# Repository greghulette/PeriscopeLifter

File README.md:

# PeriscopeLifter
Files and Basic Instructions for my Periscope Lifter

Latest version is V0.4

The latest instructions can be found here: https://docs.google.com/document/d/1gkrul7UIyUIZ05SwGsmy0yHRKMRutKzC-wxl7RRob7I/edit?usp=sharing

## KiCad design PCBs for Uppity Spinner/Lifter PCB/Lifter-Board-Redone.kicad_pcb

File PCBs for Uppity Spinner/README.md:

# PeriscopeLifter
Here are the files for the PCBs that I modified for the Open Source Periscope Lifter.  All these files were created with KiCad so you may need to download them if you want to open them, or there is a Gerber folder that you can use to have them manufactured.   

The Lifter board is a slightly modified PCB from the original one.  I had added some 5V outputs and a serial port header.  Mimir has since incorporated these into his designs.  You may use this PCB or his, providing his is utilizing the Silicone Ribbon cable.  They both perform the same function.   

The Rotary PCB is a new form factor that was desiged to work with this design.

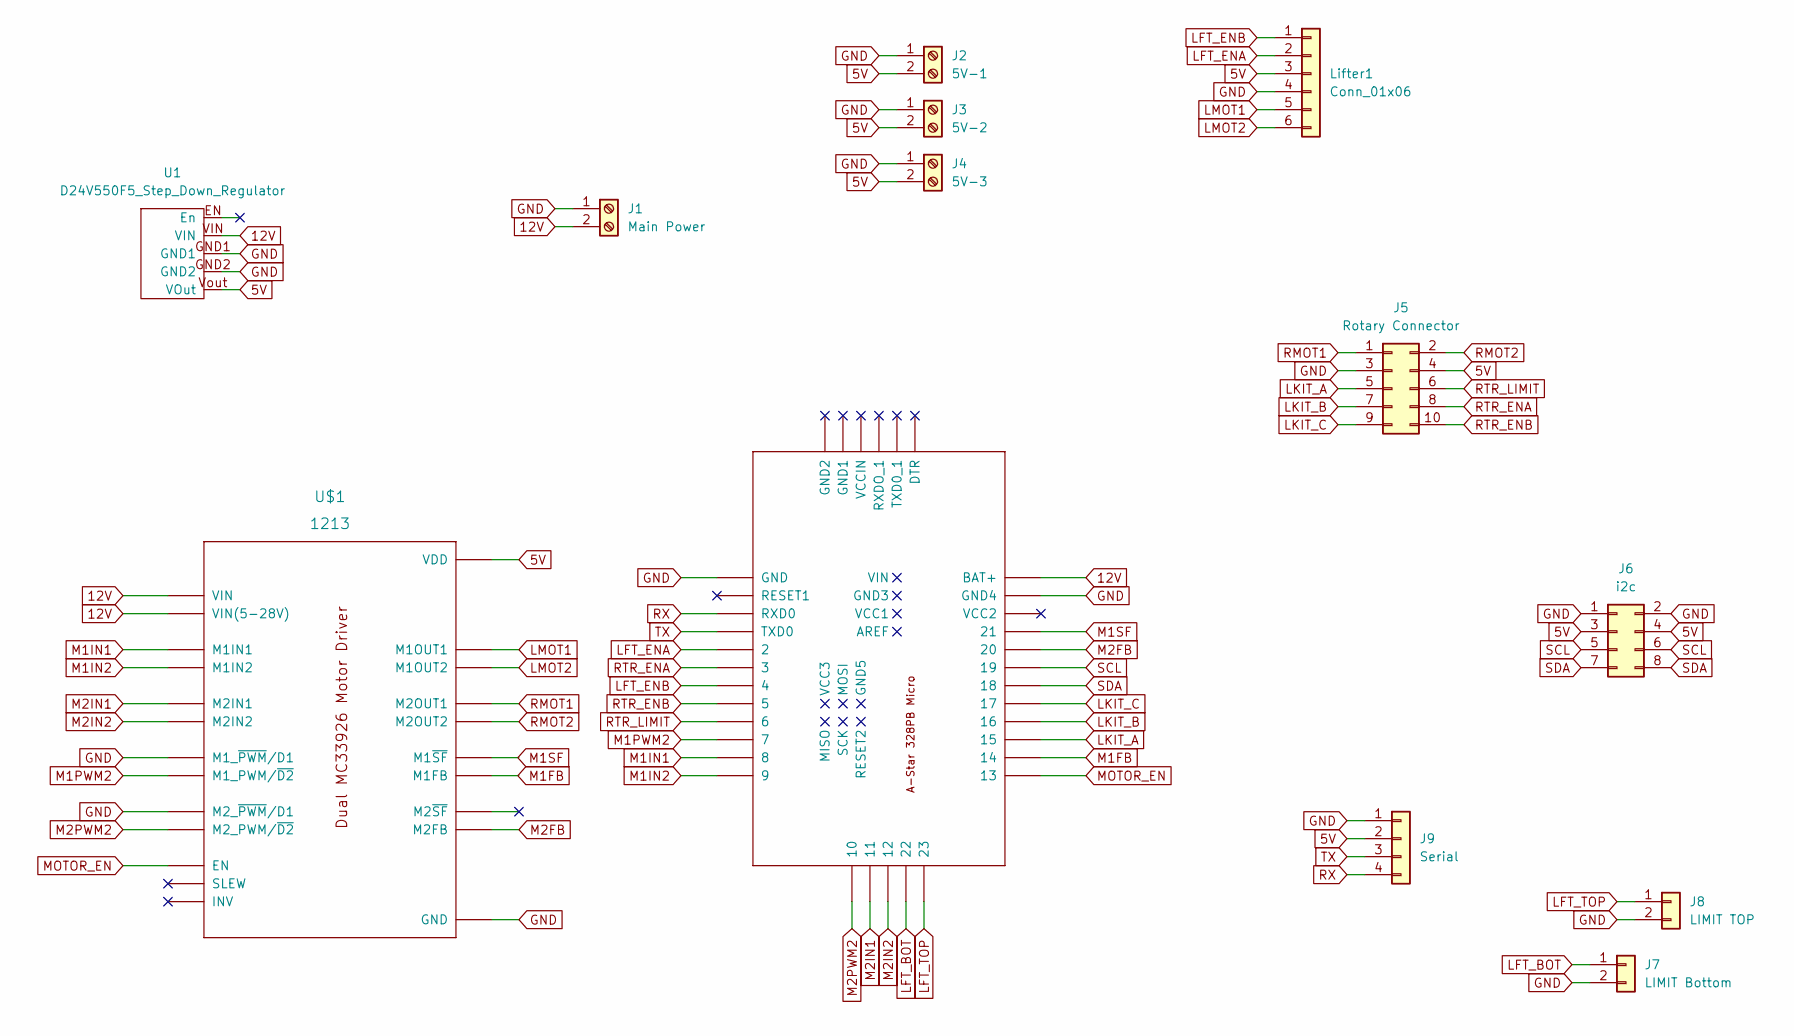
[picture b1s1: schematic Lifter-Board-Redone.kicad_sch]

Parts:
J1: Main Power; TerminalBlock_RND_205-00287_1x02_P5.08mm_Horizontal
J2: 5V-1; TerminalBlock_RND_205-00287_1x02_P5.08mm_Horizontal
J3: 5V-2; TerminalBlock_RND_205-00287_1x02_P5.08mm_Horizontal
J4: 5V-3; TerminalBlock_RND_205-00287_1x02_P5.08mm_Horizontal
J5: Rotary Connector; TE_1761607-3Uppity
J6: i2c; PinHeader_2x04_P2.54mm_Vertical
J7: LIMIT Bottom; PinHeader_1x02_P2.54mm_Vertical
J8: LIMIT TOP; PinHeader_1x02_P2.54mm_Vertical
J9: Serial; PinHeader_1x04_P2.54mm_Vertical
J$1: POLOLU3161; A-Star POLOLU3161
Lifter1: Conn_01x06; PinHeader_1x06_P2.54mm_Horizontal
U1: D24V550F5_Step_Down_Regulator; VoltageREG_2851
U$1: 1213; MC33926 Dual Motor Driver

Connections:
5V: J2.2, J3.2, J4.2, J5.4, J6.3, J6.4, J9.2, Lifter1.3, U1.Vout (VOut), U$1.VDD, U$1.VDD$1 (VDD), U$1.VDD$2 (VDD), U$1.VDD$3 (VDD), U$1.VDD$4 (VDD), U$1.VDD$5 (VDD)
12V: J1.2, J$1.BAT+, U1.VIN, U$1.MVIN (VIN(5-28V)), U$1.VIN
GND: J1.1, J2.1, J3.1, J4.1, J5.3, J6.1, J6.2, J7.2, J8.2, J9.1, J$1.GND, J$1.GND4, Lifter1.4, U1.GND1, U1.GND2, U$1.GND, U$1.GND$1 (GND), U$1.GND$2 (GND), U$1.M1PWM1 (M1_~PWM/D1), U$1.M2PWM1 (M2_~PWM/D1), U$1.MGND (GND)
LFT_BOT: J7.1, J$1.22
LFT_ENA: J$1.2, Lifter1.2
LFT_ENB: J$1.4, Lifter1.1
LFT_TOP: J8.1, J$1.23
LKIT_A: J5.5, J$1.15
LKIT_B: J5.7, J$1.16
LKIT_C: J5.9, J$1.17
LMOT1: Lifter1.5, U$1.M1OUT1
LMOT2: Lifter1.6, U$1.M1OUT2
M1FB: J$1.14, U$1.M1FB
M1IN1: J$1.8, U$1.M1IN1
M1IN2: J$1.9, U$1.M1IN2
M1PWM2: J$1.7, U$1.M1PWM2 (M1_PWM/~D2)
M1SF: J$1.21, U$1.M1SF (M1~SF)
M2FB: J$1.20, U$1.M2FB
M2IN1: J$1.11, U$1.M2IN1
M2IN2: J$1.12, U$1.M2IN2
M2PWM2: J$1.10, U$1.M2PWM2 (M2_PWM/~D2)
MOTOR_EN: J$1.13, U$1.EN
RMOT1: J5.1, U$1.M2OUT1
RMOT2: J5.2, U$1.M2OUT2
RTR_ENA: J5.8, J$1.3
RTR_ENB: J5.10, J$1.5
RTR_LIMIT: J5.6, J$1.6
RX: J9.4, J$1.RXD0
SCL: J6.5, J6.6, J$1.19
SDA: J6.7, J6.8, J$1.18
TX: J9.3, J$1.TXD0

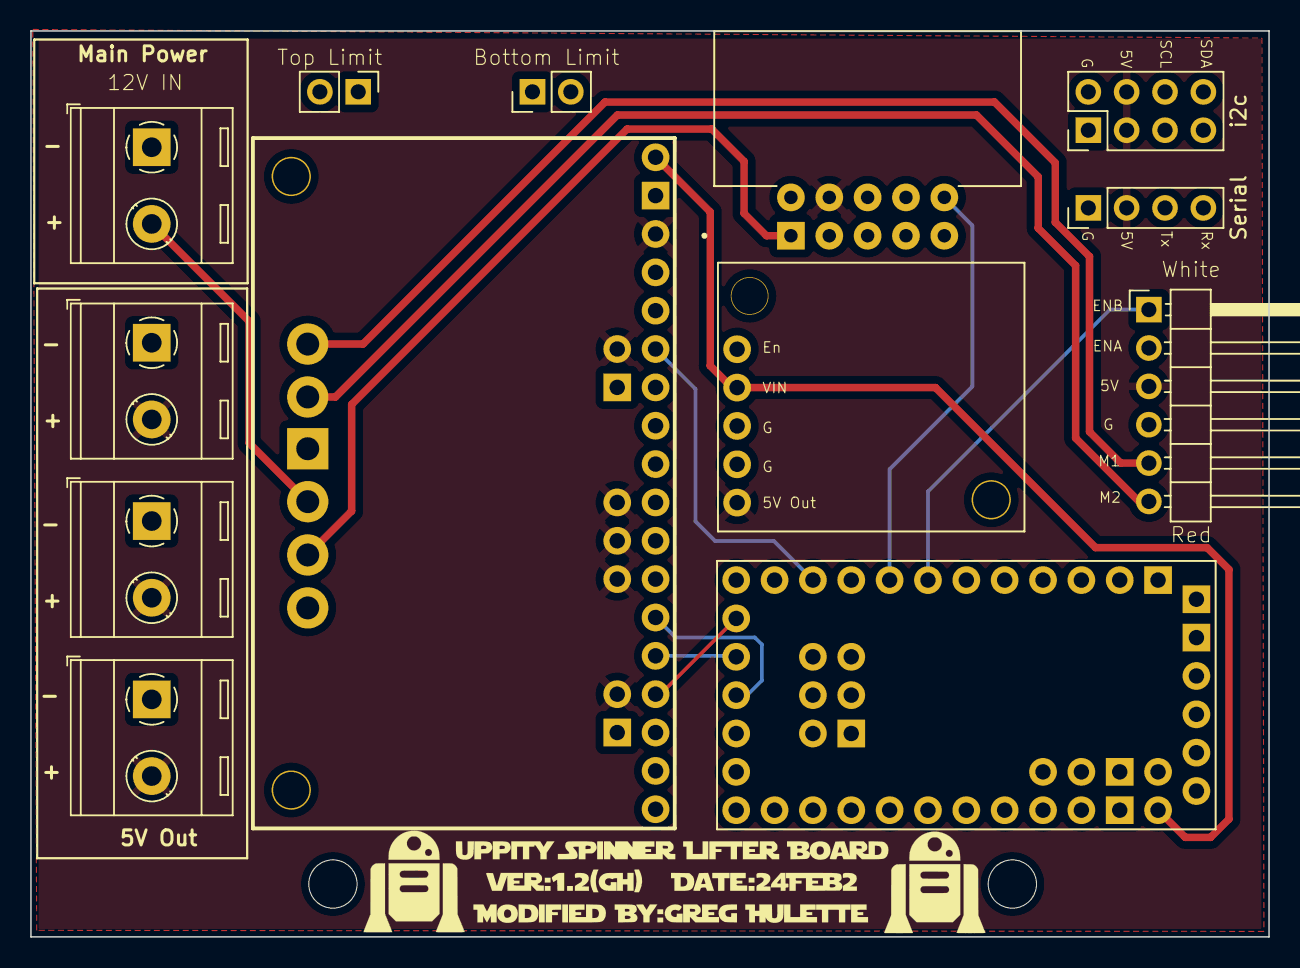
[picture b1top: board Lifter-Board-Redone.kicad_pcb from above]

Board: 4 copper layers, 82.0 x 60.0 mm, 13 parts (0 on the bottom side), 31 nets.

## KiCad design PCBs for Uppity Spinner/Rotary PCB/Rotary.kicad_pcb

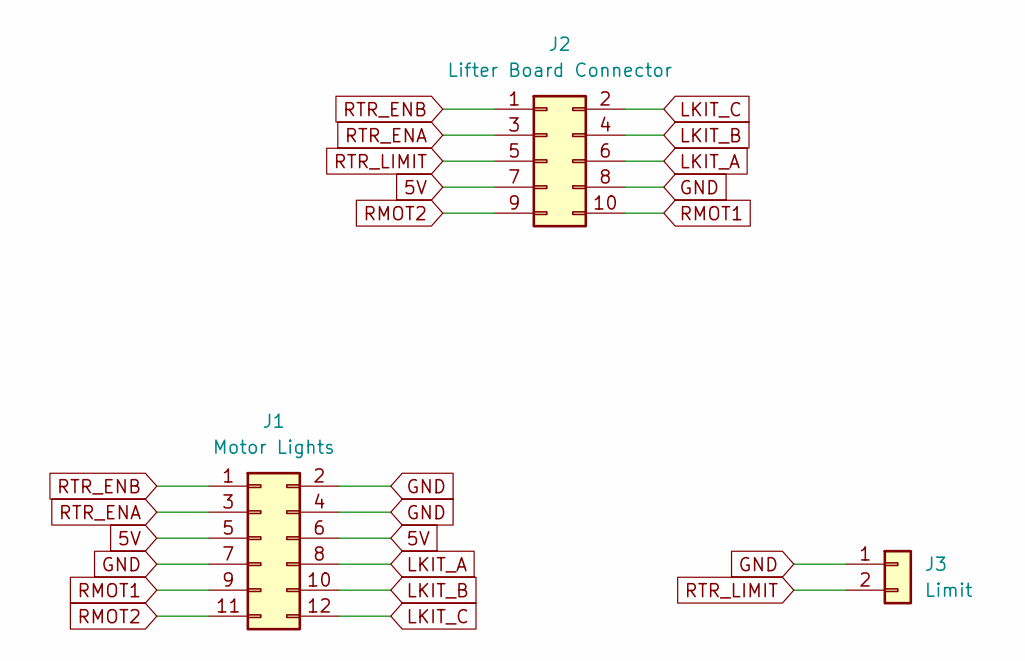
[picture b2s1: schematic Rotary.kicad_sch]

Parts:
J1: Motor Lights; PinHeader_2x06_P2.54mm_Horizontal
J2: Lifter Board Connector; TE_1761607-3Uppity
J3: Limit; PinHeader_1x02_P2.54mm_Horizontal

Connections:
5V: J1.5, J1.6, J2.7
GND: J1.2, J1.4, J1.7, J2.8, J3.1
LKIT_A: J1.8, J2.6
LKIT_B: J1.10, J2.4
LKIT_C: J1.12, J2.2
RMOT1: J1.9, J2.10
RMOT2: J1.11, J2.9
RTR_ENA: J1.3, J2.3
RTR_ENB: J1.1, J2.1
RTR_LIMIT: J2.5, J3.2

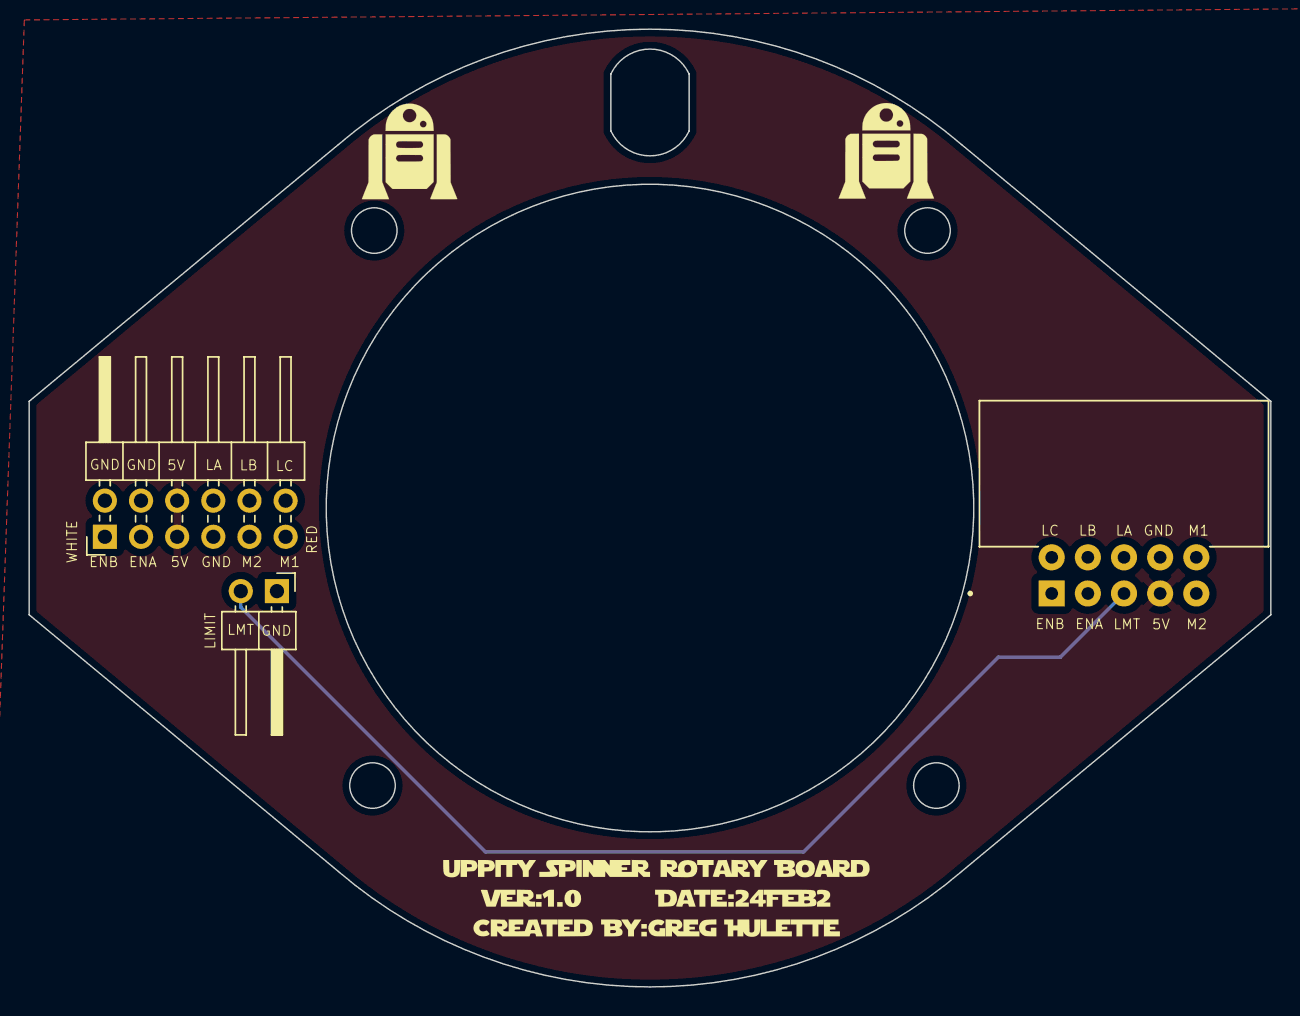
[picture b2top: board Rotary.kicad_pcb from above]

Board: 4 copper layers, 87.2 x 67.3 mm, 3 parts (0 on the bottom side), 10 nets.

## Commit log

2021-09-28 Something:
2021-09-29 uploaded the baseplate file
2021-10-15 Added files and instructions
2021-10-21 Archive
    Archived some files
2021-11-07 Added In-Line Slip Ring Breakout Board
2022-02-28 Added the Fusion 360 Files
2022-03-01 Individual Exports from Fusion 360
2022-03-02 Organized and updated files in the V0.3 Folder
2022-03-03 Updated Files and created STLs
2022-03-03 Added drill guides
2022-03-04 Updated the Nut Lock File and Added the Full Assembly
2022-03-04 Updated the Main Assembly File and adjust others
2022-03-14 Updated some files.
2022-03-25 Added the Electronics Rotary Mount
2022-03-30 Updated the Spacer for the Uppity Spinner
2022-04-04 Updated the Rotary Motor Mount
2022-04-04 Little Update to Rotary Mount
2022-04-06 Uploaded the PCB's for the Rotary and modified Lifter for the Uppity Spinner.
2022-04-06 Removed OS generated files
2022-04-06 Added step files for V 0.3
2022-06-07 Added a version to test with a larger OD/ID pipe
2022-06-13 Made a V2 folder for the larger pipe tests
2022-06-28 Nothing to see here.
2022-07-05 Updates to the larger pipe tests
2023-01-09 Created a V 0.4
2023-01-09 Updated the Read mes
2023-03-08 Removed some files in V0.4
